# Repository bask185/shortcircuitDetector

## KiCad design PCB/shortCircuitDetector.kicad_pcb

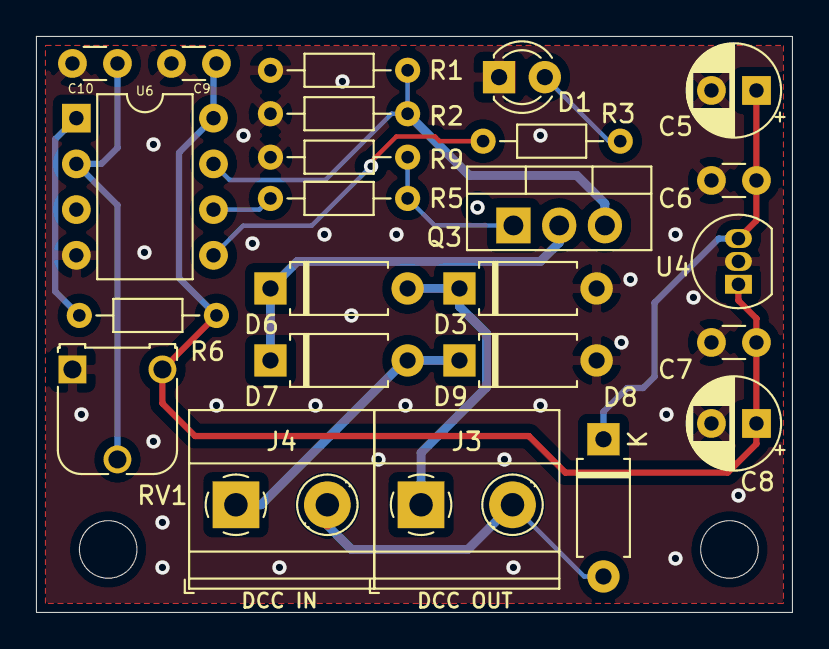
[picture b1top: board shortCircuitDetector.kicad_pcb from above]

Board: 2 copper layers, 42.0 x 32.0 mm, 24 parts (0 on the bottom side), 14 nets.

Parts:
C5, C8: CP; CP_Radial_D5.0mm_P2.50mm
C6, C7, C9, C10: C; C_Disc_D3.0mm_W1.6mm_P2.50mm
D1: LED; LED_D3.0mm
D3, D6, D7, D8, D9: D; D_A-405_P7.62mm_Horizontal
J3: AC IN; TerminalBlock_Phoenix_MKDS-1,5-2-5.08_1x02_P5.08mm_Horizont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
J4: AC_OUT; TerminalBlock_Phoenix_MKDS-1,5-2-5.08_1x02_P5.08mm_Horizont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
Q3: IRF540N; TO-220-3_Vertical
R1: 1R; R_Axial_DIN0204_L3.6mm_D1.6mm_P7.62mm_Horizontal
R2, R3, R5, R6, R9: R; R_Axial_DIN0204_L3.6mm_D1.6mm_P7.62mm_Horizontal
RV1: R_POT; Potentiometer_Runtron_RM-065_Vertical
U4: L78L05_TO92; TO-92_Inline
U6: ATtiny45-20PU; DIP-8_W7.62mm

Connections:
+5V: C7.1, C8.1, C9.2, R6.1, RV1.3, U4.1, U6.8
/adjust: C10.2, RV1.2, U6.2
/currSens: Q3.3, R1.1, R2.2, U6.7
/led: R3.1, U6.5
/on_off: R5.1, U6.6
GND: C5.2, C6.2, C7.2, C8.2, C9.1, C10.1, D1.1, D3.2, D9.2, R1.2, R2.1, R9.1, RV1.1, U4.2, U6.4
unnamed: D1.2, R3.2
unnamed: D3.1, D6.2, J3.1
unnamed: D6.1, D7.1, Q3.2
unnamed: D7.2, D9.1, J4.1
unnamed: D8.2, J3.2, J4.2
unnamed: Q3.1, R5.2, R9.2
unnamed: R6.2, U6.1
VCC: C5.1, C6.1, D8.1, U4.3

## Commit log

2022-01-18 project is compilable for an attiny45. Build script may need to be altered to use an arduino as ISP. The code should be working but values have to be examinated.
    There are debug flags present to dumb data over the serial monitor
2022-01-30 removed io.tab. This version is tested and working properly with an Arduino Nano, it has not yet been tested with an attiny45
2022-01-30 removed unneeded state machine files from src directory
